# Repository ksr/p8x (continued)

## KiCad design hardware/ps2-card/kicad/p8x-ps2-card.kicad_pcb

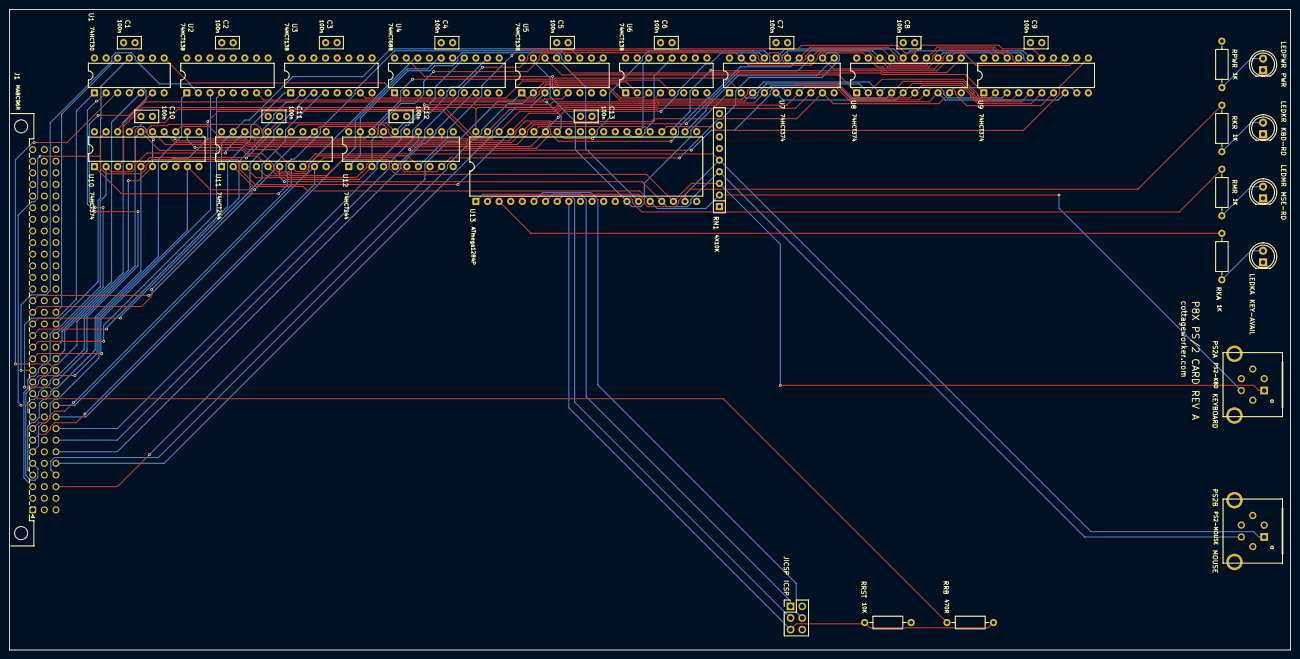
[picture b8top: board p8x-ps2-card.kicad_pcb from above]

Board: 4 copper layers, 280.0 x 140.0 mm, 41 parts (0 on the bottom side), 74 nets.

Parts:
C1, C2, C3, C4, C5, C6, C7, C8, C9, C10, C11, C12, C13: 100nF; C_Disc_D5.0mm_W2.5mm_P2.50mm
J1: MABC96R; DIN41612_C_3x32_Male_Horizontal_THT
JICSP: ICSP; PinHeader_2x03_P2.54mm_Vertical
LEDKA: GRN; LED_D5.0mm
LEDKR: YEL; LED_D5.0mm
LEDMR: YEL; LED_D5.0mm
LEDPWR: GRN; LED_D5.0mm
PS2A: PS2-KBD; MiniDIN6_RA_PS2
PS2B: PS2-MOUSE; MiniDIN6_RA_PS2
RKA: 1K; R_Axial_DIN0207_L6.3mm_D2.5mm_P10.16mm_Horizontal
RKR: 1K; R_Axial_DIN0207_L6.3mm_D2.5mm_P10.16mm_Horizontal
RMR: 1K; R_Axial_DIN0207_L6.3mm_D2.5mm_P10.16mm_Horizontal
RN1: 4X10K; R_Array_SIP9
RPWR: 1K; R_Axial_DIN0207_L6.3mm_D2.5mm_P10.16mm_Horizontal
RRB: 470R; R_Axial_DIN0207_L6.3mm_D2.5mm_P10.16mm_Horizontal
RRST: 10K; R_Axial_DIN0207_L6.3mm_D2.5mm_P10.16mm_Horizontal
U1: 74HCT30; DIP-14_W7.62mm
U2, U3, U5, U6: 74HCT138; DIP-16_W7.62mm
U4: 74HCT688; DIP-20_W7.62mm
U7, U8, U9, U10: 74HCT374; DIP-20_W7.62mm
U11, U12: 74HCT244; DIP-20_W7.62mm
U13: ATmega1284P; DIP-40_W15.24mm

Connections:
-MEMW: U3.7, U6.5
-PSSEL: U4.19, U5.4, U6.4
-RD: U2.7, U5.5
-RES: J1.a11, RRB.1
-RESET: JICSP.5, RRB.2, RRST.1, U13.9
-RR0: U5.15, U7.1, U13.14
-RR1: U5.14, U8.1
-RR2: U5.13, U9.1, U13.15
-RR3: U5.12, U10.1
-RR4: U5.11, U11.1, U11.19
-RR6: U5.9, U12.1, U12.19
-WR1: U6.14, U13.26
-WR3: U6.12, U13.27
A0: J1.c3, U5.1, U6.1
A1: J1.c4, U5.2, U6.2
A2: J1.c5, U5.3, U6.3
A3: J1.c6, U4.8
A4: J1.c7, U4.12
A5: J1.c8, U4.14
A6: J1.c9, U4.16
A7: J1.c10, U4.18
A8: J1.c11, U1.1
A9: J1.c12, U1.2
A10: J1.c13, U1.3
A11: J1.c14, U1.4
A12: J1.c15, U1.5
A13: J1.c16, U1.6
A14: J1.c17, U1.11
A15: J1.c18, U1.12
D0: J1.a3, U7.2, U8.2, U9.2, U10.2, U11.18, U12.18
D1: J1.a4, U7.5, U8.5, U9.5, U10.5, U11.16, U12.16
D2: J1.a5, U7.6, U8.6, U9.6, U10.6, U11.14, U12.14
D3: J1.a6, U7.9, U8.9, U9.9, U10.9, U11.12, U12.12
D4: J1.a7, U7.12, U8.12, U9.12, U10.12, U11.9, U12.9
D5: J1.a8, U7.15, U8.15, U9.15, U10.15, U11.7, U12.7
D6: J1.a9, U7.16, U8.16, U9.16, U10.16, U11.5, U12.5
D7: J1.a10, U7.19, U8.19, U9.19, U10.19, U11.3, U12.3
DLD0: J1.a16, U3.1
DLD1: J1.a17, U3.2
DLD2: J1.a18, U3.3
DLD3: J1.a19, U3.4
DOE0: J1.a12, U2.1
DOE1: J1.a13, U2.2
DOE2: J1.a14, U2.3
DOE3: J1.a15, U2.4
GND: C1.2, C2.2, C3.2, C4.2, C5.2, C6.2, C7.2, C8.2, C9.2, C10.2, C11.2, C12.2, C13.2, J1.a31, J1.a32, J1.b3, J1.b5, J1.b7, J1.b9, J1.b11, J1.b13, J1.b15, J1.b17, J1.b19, J1.b21, J1.b23, J1.b25, J1.b31, J1.b32, J1.c31, J1.c32, JICSP.6, LEDKA.1, LEDKR.1, LEDMR.1, LEDPWR.1, PS2A.3, PS2A.SH, PS2B.3, PS2B.SH, U1.7, U2.5, U2.8, U3.5, U3.8, U4.2, U4.3, U4.4, U4.5, U4.6, U4.7, U4.10, U4.13, U4.17, U5.8, U6.8, U7.10, U8.10, U9.10, U10.10, U11.10, U11.11, U11.13, U11.15, U11.17, U12.6, U12.10, U12.11, U12.13, U12.17, U13.11, U13.31
IOPG: U1.8, U4.1
LDA: U7.11, U13.22
LDB: U9.11, U13.24
LDSA: U8.11, U13.23
LDSB: U10.11, U13.25
LKA: RKA.2, U13.3
LKAA: LEDKA.2, RKA.1
LKR: RKR.2, U13.1
LKRA: LEDKR.2, RKR.1
LMR: RMR.2, U13.2
LMRA: LEDMR.2, RMR.1
LPWRA: LEDPWR.2, RPWR.1
MB0: U7.3, U8.3, U9.3, U10.3, U13.40
MB1: U7.4, U8.4, U9.4, U10.4, U13.39
MB2: U7.7, U8.7, U9.7, U10.7, U13.38
MB3: U7.8, U8.8, U9.8, U10.8, U13.37
MB4: U7.13, U8.13, U9.13, U10.13, U13.36
MB5: U7.14, U8.14, U9.14, U10.14, U13.35
MB6: U7.17, U8.17, U9.17, U10.17, U13.34
MB7: U7.18, U8.18, U9.18, U10.18, U13.33
MISO: JICSP.1, U13.7
MOSI: JICSP.4, U13.6
PS2CKA: PS2A.5, RN1.2, U11.2, U13.16
PS2CKB: PS2B.5, RN1.4, U11.6, U13.17
PS2DA: PS2A.1, RN1.3, U11.4, U13.18
PS2DB: PS2B.1, RN1.5, U11.8, U13.19
SCK: JICSP.3, U13.8
VCC: C1.1, C2.1, C3.1, C4.1, C5.1, C6.1, C7.1, C8.1, C9.1, C10.1, C11.1, C12.1, C13.1, J1.a1, J1.a2, J1.b1, J1.b2, J1.c1, J1.c2, JICSP.2, PS2A.4, PS2B.4, RN1.1, RPWR.2, RRST.2, U1.14, U2.6, U2.16, U3.6, U3.16, U4.9, U4.11, U4.15, U4.20, U5.6, U5.16, U6.6, U6.16, U7.20, U8.20, U9.20, U10.20, U11.20, U12.2, U12.4, U12.8, U12.15, U12.20, U13.10, U13.30

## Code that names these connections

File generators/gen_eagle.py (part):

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        if n in (27,28,29,30): return {27:"CLRC",28:"BSEL",29:"IRQ",30:"SPARE11"}[n]
        # B3-26: alternate ground guard (odd pins) / spare line (even pins). The
        # odd-pin grounds still shield between the data bus (row A) and address
        # bus (row C); the 12 even pins are SPARE12..23 — usable later with no
        # backplane respin.
        if 3<=n<=26 and n%2==0: return "SPARE%d"%(12+(n-4)//2)
        return "GND"
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        if n==11: return "-RES"
        if 12<=n<=15: return "DOE%d"%(n-12)
        if 16<=n<=19: return "DLD%d"%(n-16)
        return {20:"PSEL0",21:"PSEL1",22:"PINC",23:"PDEC",24:"CLK",25:"CLKB",26:"LDF",
                27:"FC",28:"FZ",29:"FN",30:"FV"}.get(n)
    if 3<=n<=18: return "A%d"%(n-3)
    if 19<=n<=22: return "ALUS%d"%(n-19)
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D("JMP2X3",[str(k) for k in range(1,7)],[],{str(k):str(k) for k in range(1,7)},"HDR2X3")    # RX/TX swap block
# ATmega328P (DIP-28 narrow): PS/2 signal processor. Standard AVR DIP pinout.
D("ATMEGA328",
  ["!RESET","PD0","PD1","PD2","PD3","PD4","PB6","PB7","PD5","PD6","PD7",
   "PB0","PB1","PB2","PB3","PB4","PB5","AREF","PC0","PC1","PC2","PC3","PC4","PC5"],
  ["VCC","AVCC","GND","GND2"],
  {"!RESET":"1","PD0":"2","PD1":"3","PD2":"4","PD3":"5","PD4":"6","VCC":"7","GND":"8",
   "PB6":"9","PB7":"10","PD5":"11","PD6":"12","PD7":"13","PB0":"14","PB1":"15","PB2":"16",
   "PB3":"17","PB4":"18","PB5":"19","AVCC":"20","AREF":"21","GND2":"22","PC0":"23","PC1":"24",
   "PC2":"25","PC3":"26","PC4":"27","PC5":"28"},"DIP28N")
# 74HC688 8-bit magnitude comparator -- the PS/2 window ($FF58-5F) address compare.
D("74688",["!G","P0","Q0","P1","Q1","P2","Q2","P3","Q3","Q4","P4","Q5","P5","Q6","P6","Q7","P7"],
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# ATmega1284P (PDIP-40, 0.6"): PS/2 signal processor. 32 GPIO (4 full ports) leaves
# ~12 spare after the bus bridge -- enough to drive the status LEDs straight off the
# MCU and leave room for host->device TX + an IRQ line (no 74123 one-shot needed).
# SPI/ICSP is on PB5(MOSI)/PB6(MISO)/PB7(SCK). Internal RC osc -> XTAL pins unused.
D("ATMEGA1284",
  ["PB0","PB1","PB2","PB3","PB4","PB5","PB6","PB7","!RESET","XTAL2","XTAL1",
   "PD0","PD1","PD2","PD3","PD4","PD5","PD6","PD7","PC0","PC1","PC2","PC3","PC4","PC5",
   "PC6","PC7","AREF","PA7","PA6","PA5","PA4","PA3","PA2","PA1","PA0"],
  ["VCC","GND","AVCC","GND2"],
  {"PB0":"1","PB1":"2","PB2":"3","PB3":"4","PB4":"5","PB5":"6","PB6":"7","PB7":"8",
   "!RESET":"9","VCC":"10","GND":"11","XTAL2":"12","XTAL1":"13","PD0":"14","PD1":"15",
   "PD2":"16","PD3":"17","PD4":"18","PD5":"19","PD6":"20","PD7":"21","PC0":"22","PC1":"23",
   "PC2":"24","PC3":"25","PC4":"26","PC5":"27","PC6":"28","PC7":"29","AVCC":"30","GND2":"31",
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        # A part hard against the bottom edge (the backplane's R1/LED1 sit at
        # y=3.0) would push its value off the board, where it simply doesn't get
        # printed. Stack it above the name instead. Moving the part is not an
        # option -- the LED_A routing is pinned to it -- and this is silk only.
        if not unplaced and _ty_val < 0.5:
            _ty_val = _ty_name+1.778+0.6
        o.append(f'<element name="{ref}" library="p8x" package="{DEV[dev]["pkg"]}" value="{val}" x="{ex:.2f}" y="{ey:.2f}"{rot} smashed="yes">')
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# rev B 32-bit control word -> pipeline latches U14..U17 (8 bits each).
# Word bit b is latch U[14 + b//8], output Q[(b%8)+1].
PIPE={14:["DOE0","DOE1","DOE2","DOE3","DLD0","DLD1","DLD2","DLD3"],
 15:["PSEL0","PSEL1","PSEL2","PINC","PDEC","ALUS0","ALUS1","ALUS2"],
 16:["ALUS3","ALUM","CIN","SH0","SH1","LDF","FCOND0","FCOND1"],
 17:["FCOND2","URST","HALT","LDZN","SHCIN","SETC","CLRC","BSEL"]}
for k,sigs in PIPE.items():
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N(n,"LEDRN",("R4","2"),("LED4","A")); N(n,"LEDHL",("R5","2"),("LED5","A"))
card("control-card","P8X CONTROL/MICROCODE CARD REV B",ic,sm,n,
 {"D%d"%i for i in range(8)}|{"DOE%d"%i for i in range(4)}|{"DLD%d"%i for i in range(4)}|
 {"PSEL0","PSEL1","PSEL2","PINC","PDEC","ALUS0","ALUS1","ALUS2","ALUS3","ALUM","CIN","SH0","SH1",
  "LDF","CLK","CLKB","-RES","FC","FZ","FN","FV","LDZN","SHCIN","SETC","CLRC","BSEL","IRQ"},
 labels={"U19":"N^V XOR"})

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N(n,"VCC",("U39","G1")); N(n,"GND",("U39","!G2B"))
N(n,"CNTN",("U34","1Y"),("U39","!G2A"))
for p in range(6): N(n,"-CNT%d"%p,("U39","Y%d"%p))
N(n,"PINC",("U34","1A")); N(n,"PDEC",("U34","1B"),("U35","1A"))
N(n,"UDB",("U35","1Y"))
N(n,"GND",*[("U34",p) for p in ("2A","2B","3A","3B","4A","4B")],
  *[("U35",p) for p in ("3A","4A","5A","6A")],
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N(n,"LEDRD",("R4","2"),("LED4","A")); N(n,"LEDLD",("R5","2"),("LED5","A"))
# PT (PSEL=4) and PT2 (PSEL=5) scratch pointers -- rev D. Both are now four
# 74169 counters each (identical structure to P0-P3, a carry chain on !RCO->!ENT)
# so the 16-bit ops can PINC them, loaded from D0-7 on -LDLp/-LDHp and driven
# onto the pointer bus PB via two 74244 select buffers gated by -SELp. Counter
# numbering: PT=U41-44, PT2=U45-48; select buffers PT=U49/50, PT2=U51/52.
for p in (4,5):
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card("regbank-card","P8X REGISTER BANK CARD REV D (P0=PC P3=SP, PT+PT2 scratch counters)",ic,sm,n,
 {"D%d"%i for i in range(8)}|{"A%d"%i for i in range(16)}|
 {"DLD%d"%i for i in range(4)}|{"DOE%d"%i for i in range(4)}|
 {"PSEL0","PSEL1","PSEL2","PINC","PDEC","CLK","-RES"})

# ===================== ALU CARD ===============================================
n={}
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N(n,"TXD",("U14","TXD"),("U8","T1IN"))
N(n,"RXD",("U14","RXD"),("U8","R1OUT"))
# ACIA1 RS-232 through the RX/TX swap jumper JP1 to DB9-A. Center pins 3/4 = the
# MAX232 side (SOUT/SIN); pins 1/6 = DB9.3 (TXD), pins 2/5 = DB9.2 (RXD). A pair of
# shunts selects straight-through (DTE) or crossed (null-modem).
N(n,"SOUT",("U8","T1OUT"),("JP1","3")); N(n,"SIN",("U8","R1IN"),("JP1","4"))
N(n,"S1TXD",("JP1","1"),("JP1","6"),("DB9A","3")); N(n,"S1RXD",("JP1","2"),("JP1","5"),("DB9A","2"))
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N(pcn,"-WR1",("U27","Y1"),("U24","PC4"))                 # PSAST write -> '328 sense
N(pcn,"-WR3",("U27","Y3"),("U24","PC5"))                 # PSBST write -> '328 sense
# read latches: D = '328 MB[0:7] bus, Q -> P8X D0-7, CLK from '328 load lines
_MB=["PB0","PB1","PB2","PB3","PB4","PB5","PD6","PD7"]
for b in range(8):
    N(pcn,"MB%d"%b,("U24",_MB[b]),
      ("U28","D%d"%(b+1)),("U29","D%d"%(b+1)),("U30","D%d"%(b+1)),("U31","D%d"%(b+1)))
    N(pcn,"D%d"%b,("U28","Q%d"%(b+1)),("U29","Q%d"%(b+1)),("U30","Q%d"%(b+1)),
      ("U31","Q%d"%(b+1)),("U32","Y%d"%(b+1)),("U33","Y%d"%(b+1)))
N(pcn,"LDA",("U24","PC0"),("U28","CLK")); N(pcn,"LDSA",("U24","PC1"),("U29","CLK"))
N(pcn,"LDB",("U24","PC2"),("U30","CLK")); N(pcn,"LDSB",("U24","PC3"),("U31","CLK"))
# PSLINE buffer: 4 live PS/2 lines -> D0-3; D4-7 strapped low
N(pcn,"PS2CKA",("U32","A1")); N(pcn,"PS2DA",("U32","A2"))
N(pcn,"PS2CKB",("U32","A3")); N(pcn,"PS2DB",("U32","A4"))
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N(pcn,"VCC",("U33","A1"),("U33","A2"),("U33","A4"),("U33","A7"))
N(pcn,"GND",("U33","A3"),("U33","A5"),("U33","A6"),("U33","A8"))
# ATmega328 PS/2 lines, power, reset/ICSP. VCC(7)/GND(8) auto-wired by card().
N(pcn,"PS2CKA",("U24","PD2")); N(pcn,"PS2DA",("U24","PD4"))
N(pcn,"PS2CKB",("U24","PD3")); N(pcn,"PS2DB",("U24","PD5"))
N(pcn,"VCC",("U24","AVCC")); N(pcn,"GND",("U24","GND2"))
N(pcn,"PS2CKA",("PS2A","5")); N(pcn,"PS2DA",("PS2A","1"))
N(pcn,"GND",("PS2A","3")); N(pcn,"VCC",("PS2A","4"))
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N(pcn,"VCC",("RN3","COM"))
N(pcn,"PS2CKA",("RN3","R1")); N(pcn,"PS2DA",("RN3","R2"))
N(pcn,"PS2CKB",("RN3","R3")); N(pcn,"PS2DB",("RN3","R4"))
# ICSP (AVR 2x3): 1 MISO(PB4/MB4) 2 VCC 3 SCK(PB5/MB5) 4 MOSI(PB3/MB3) 5 !RESET 6 GND
N(pcn,"MB4",("JICSP","1")); N(pcn,"VCC",("JICSP","2")); N(pcn,"MB5",("JICSP","3"))
N(pcn,"MB3",("JICSP","4")); N(pcn,"-RESET",("JICSP","5"),("U24","!RESET"),("RRST","1"))
N(pcn,"GND",("JICSP","6")); N(pcn,"VCC",("RRST","2"))
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      ("U7","D%d"%(b+1)),("U8","D%d"%(b+1)),("U9","D%d"%(b+1)),("U10","D%d"%(b+1)))
    N(n,"D%d"%b,("U7","Q%d"%(b+1)),("U8","Q%d"%(b+1)),("U9","Q%d"%(b+1)),
      ("U10","Q%d"%(b+1)),("U11","Y%d"%(b+1)),("U12","Y%d"%(b+1)))
N(n,"LDA",("U13","PC0"),("U7","CLK")); N(n,"LDSA",("U13","PC1"),("U8","CLK"))
N(n,"LDB",("U13","PC2"),("U9","CLK")); N(n,"LDSB",("U13","PC3"),("U10","CLK"))
# PSLINE buffer: 4 live PS/2 lines -> D0-3; D4-7 strapped low
N(n,"PS2CKA",("U11","A1")); N(n,"PS2DA",("U11","A2"))
N(n,"PS2CKB",("U11","A3")); N(n,"PS2DB",("U11","A4"))
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N(n,"VCC",("U12","A1"),("U12","A2"),("U12","A4"),("U12","A7"))
N(n,"GND",("U12","A3"),("U12","A5"),("U12","A6"),("U12","A8"))
# ATmega1284 PS/2 lines, power. VCC(10)/GND(11) auto-wired by card(); tie AVCC + 2nd GND.
N(n,"PS2CKA",("U13","PD2")); N(n,"PS2DA",("U13","PD4"))
N(n,"PS2CKB",("U13","PD3")); N(n,"PS2DB",("U13","PD5"))
N(n,"VCC",("U13","AVCC")); N(n,"GND",("U13","GND2"))
# status LEDs, driven straight off the MCU (no one-shot -- firmware stretches the
# blink): PB0 = keyboard-read activity, PB1 = mouse-read activity, PB2 = keystroke
# available (lit while a kbd byte waits). Plus a plain power LED on VCC.
N(n,"LKR",("U13","PB0"),("RKR","2")); N(n,"LKRA",("RKR","1"),("LEDKR","A")); N(n,"GND",("LEDKR","K"))
N(n,"LMR",("U13","PB1"),("RMR","2")); N(n,"LMRA",("RMR","1"),("LEDMR","A")); N(n,"GND",("LEDMR","K"))
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
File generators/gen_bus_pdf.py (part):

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        if n==11: return "-RES"
        if 12<=n<=15: return "DOE%d"%(n-12)
        if 16<=n<=19: return "DLD%d"%(n-16)
        return {20:"PSEL0",21:"PSEL1",22:"PINC",23:"PDEC",24:"CLK",25:"CLKB",26:"LDF",27:"FC",28:"FZ",29:"FN",30:"FV"}.get(n)
    if 3<=n<=18: return "A%d"%(n-3)
    if 19<=n<=22: return "ALUS%d"%(n-19)
    return {23:"ALUM",24:"CIN",25:"SH0",26:"SH1",
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 "FV":"Flag: oVerflow (signed, rev C: sign-bit method on the ALU card). ALU card to control card, as FC",
 "+5V":"Power, 6 pins total","GND":"Ground / row-B guard",
 "-RES":"System reset, active low","CLK":"System clock","CLKB":"Inverted clock",
 "LDF":"Latch flags (ALU card)","PINC":"Selected pointer increment",
 "PDEC":"Selected pointer decrement","ALUM":"74181 mode (logic/arith)",
 "CIN":"ALU carry in","SH0":"Shifter control 0","SH1":"Shifter control 1",
 "PSEL2":"Pointer-select bit 2 (P0-P3, PT scratch=4, PT2 scratch=5 since reg-bank rev D); to reg-bank",
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 "28&nbsp;mm pitch, 4-layer (signals / GND plane / +5V plane / signals). "
 "Power: A1,B1,C1,A2,B2,C2 = +5V; A31,B31,C31,A32,B32,C32 = GND. "
 "Row B pins 3&ndash;26 alternate: odd pins are a grounded guard between the two "
 "signal rows, even pins are spare bus lines SPARE12&ndash;23; B27&ndash;30 carry signals. "
 "This table is generated from the same pin-map function used by the CAD "
 "generators, so it cannot drift from the board files.", N))
story.append(Spacer(1,10))
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leg=[["Acronym","Meaning","Acronym","Meaning"],
 ["Dn","Data bus, bit n (8-bit)","An","Address bus, bit n (16-bit)"],
 ["DOE0-3","Data Output Enable field: selects\nwhich card drives the data bus","DLD0-3","Data LoaD field: selects which\nregister latches the data bus"],
 ["PSEL0-2","Pointer SELect: which of P0-P3\n(PC/ptr/ptr/SP), PT or PT2 is active","PINC / PDEC","Pointer INCrement / DECrement\n(applies to selected pointer)"],
 ["ALUS0-3","74181 ALU function Select lines","ALUM","74181 Mode: logic vs arithmetic"],
 ["CIN","ALU Carry IN","SH0-1","SHifter control (pass/left/right/rotate)"],
 ["LDF","LoaD Flags: latch C,Z,N,V from ALU","-RES","RESet, active low (_N = active low)"],
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    return ", ".join(p) if len(p)<=6 else "%s ... %s (%d pins)"%(p[0],p[-1],len(p))
order=(["D%d"%i for i in range(8)]+["A%d"%i for i in range(16)]
 +["DOE%d"%i for i in range(4)]+["DLD%d"%i for i in range(4)]
 +["PSEL0","PSEL1","PSEL2","PINC","PDEC","LDF","ALUS0","ALUS1","ALUS2","ALUS3","ALUM",
   "CIN","SH0","SH1","CLK","CLKB","-RES","LDZN","SHCIN","SETC","CLRC","BSEL"]
 +["FC","FZ","FN","FV"]
 +["IRQ","SPARE11"]+["+5V","GND"])
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 "4. Address bus is driven exclusively by the register-bank card (selected pointer).",
 "5. rev C3: C27-C30 = PSEL2/LDZN/SHCIN/SETC and B27 = CLRC (were SPARE4-8). rev C: B28 = BSEL (ALU B-mux select, was SPARE9), B29 = IRQ (interrupt request, was SPARE10); SPARE11 (B30) remains reserved.",
 "5b. SPARE0-3 were reallocated as flag lines FC/FZ/FN/FV (A27-A30). SPARE numbering therefore starts at 4.",
 "5c. Row B: odd pins B3-B25 are ground guards, even pins B4-B26 are SPARE12-23; B27 = CLRC, B28 = BSEL, B29 = IRQ, B30 = SPARE11.",
 "6. Verify row A/C orientation against physical DIN connectors before first fab."]:
    story.append(Paragraph(note,N))
doc.build(story)
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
